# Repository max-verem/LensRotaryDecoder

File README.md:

# Lens Rotary Decoder

This project cover several cases on getting lens rotation info

## EZ-USB with Canon HJ14ex4.3B

This version cover getting virtual output of Canon HJ14ex4.3B lens output, please [follow](EZ-USB.md) detailed description

## MCU version

This version cover getting virtual output of Canon HJ14ex4.3B lens output and stanalone encoders, please [follow](MCU-NET.md) detailed description

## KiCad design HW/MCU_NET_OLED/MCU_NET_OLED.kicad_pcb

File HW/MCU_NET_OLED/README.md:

# MCU version of rotary decoder

This version cover both cases:
* Canon HJ14ex4.3B lens virtual output encoder
* Standalone rotary encoders

## Schematic

## PCB

[gerber file](gerber/)

## Firmware

* [rotary decoder firmware source](../../STM32/STM32F411CEU6_RotaryDecoder_3X)
* [NET OLED interface firmware source](../../STM32/STM32F411CEU6_FPGA_UART)

## Hardcoded things

* MAC address of this device is **BA:DE:C0:DE:XX:00** where **XX* is a *unique* hex value for that board
* IP address of FreeD receiver is broadcast (255.255.255.255), destination port is **60000** + **XX**

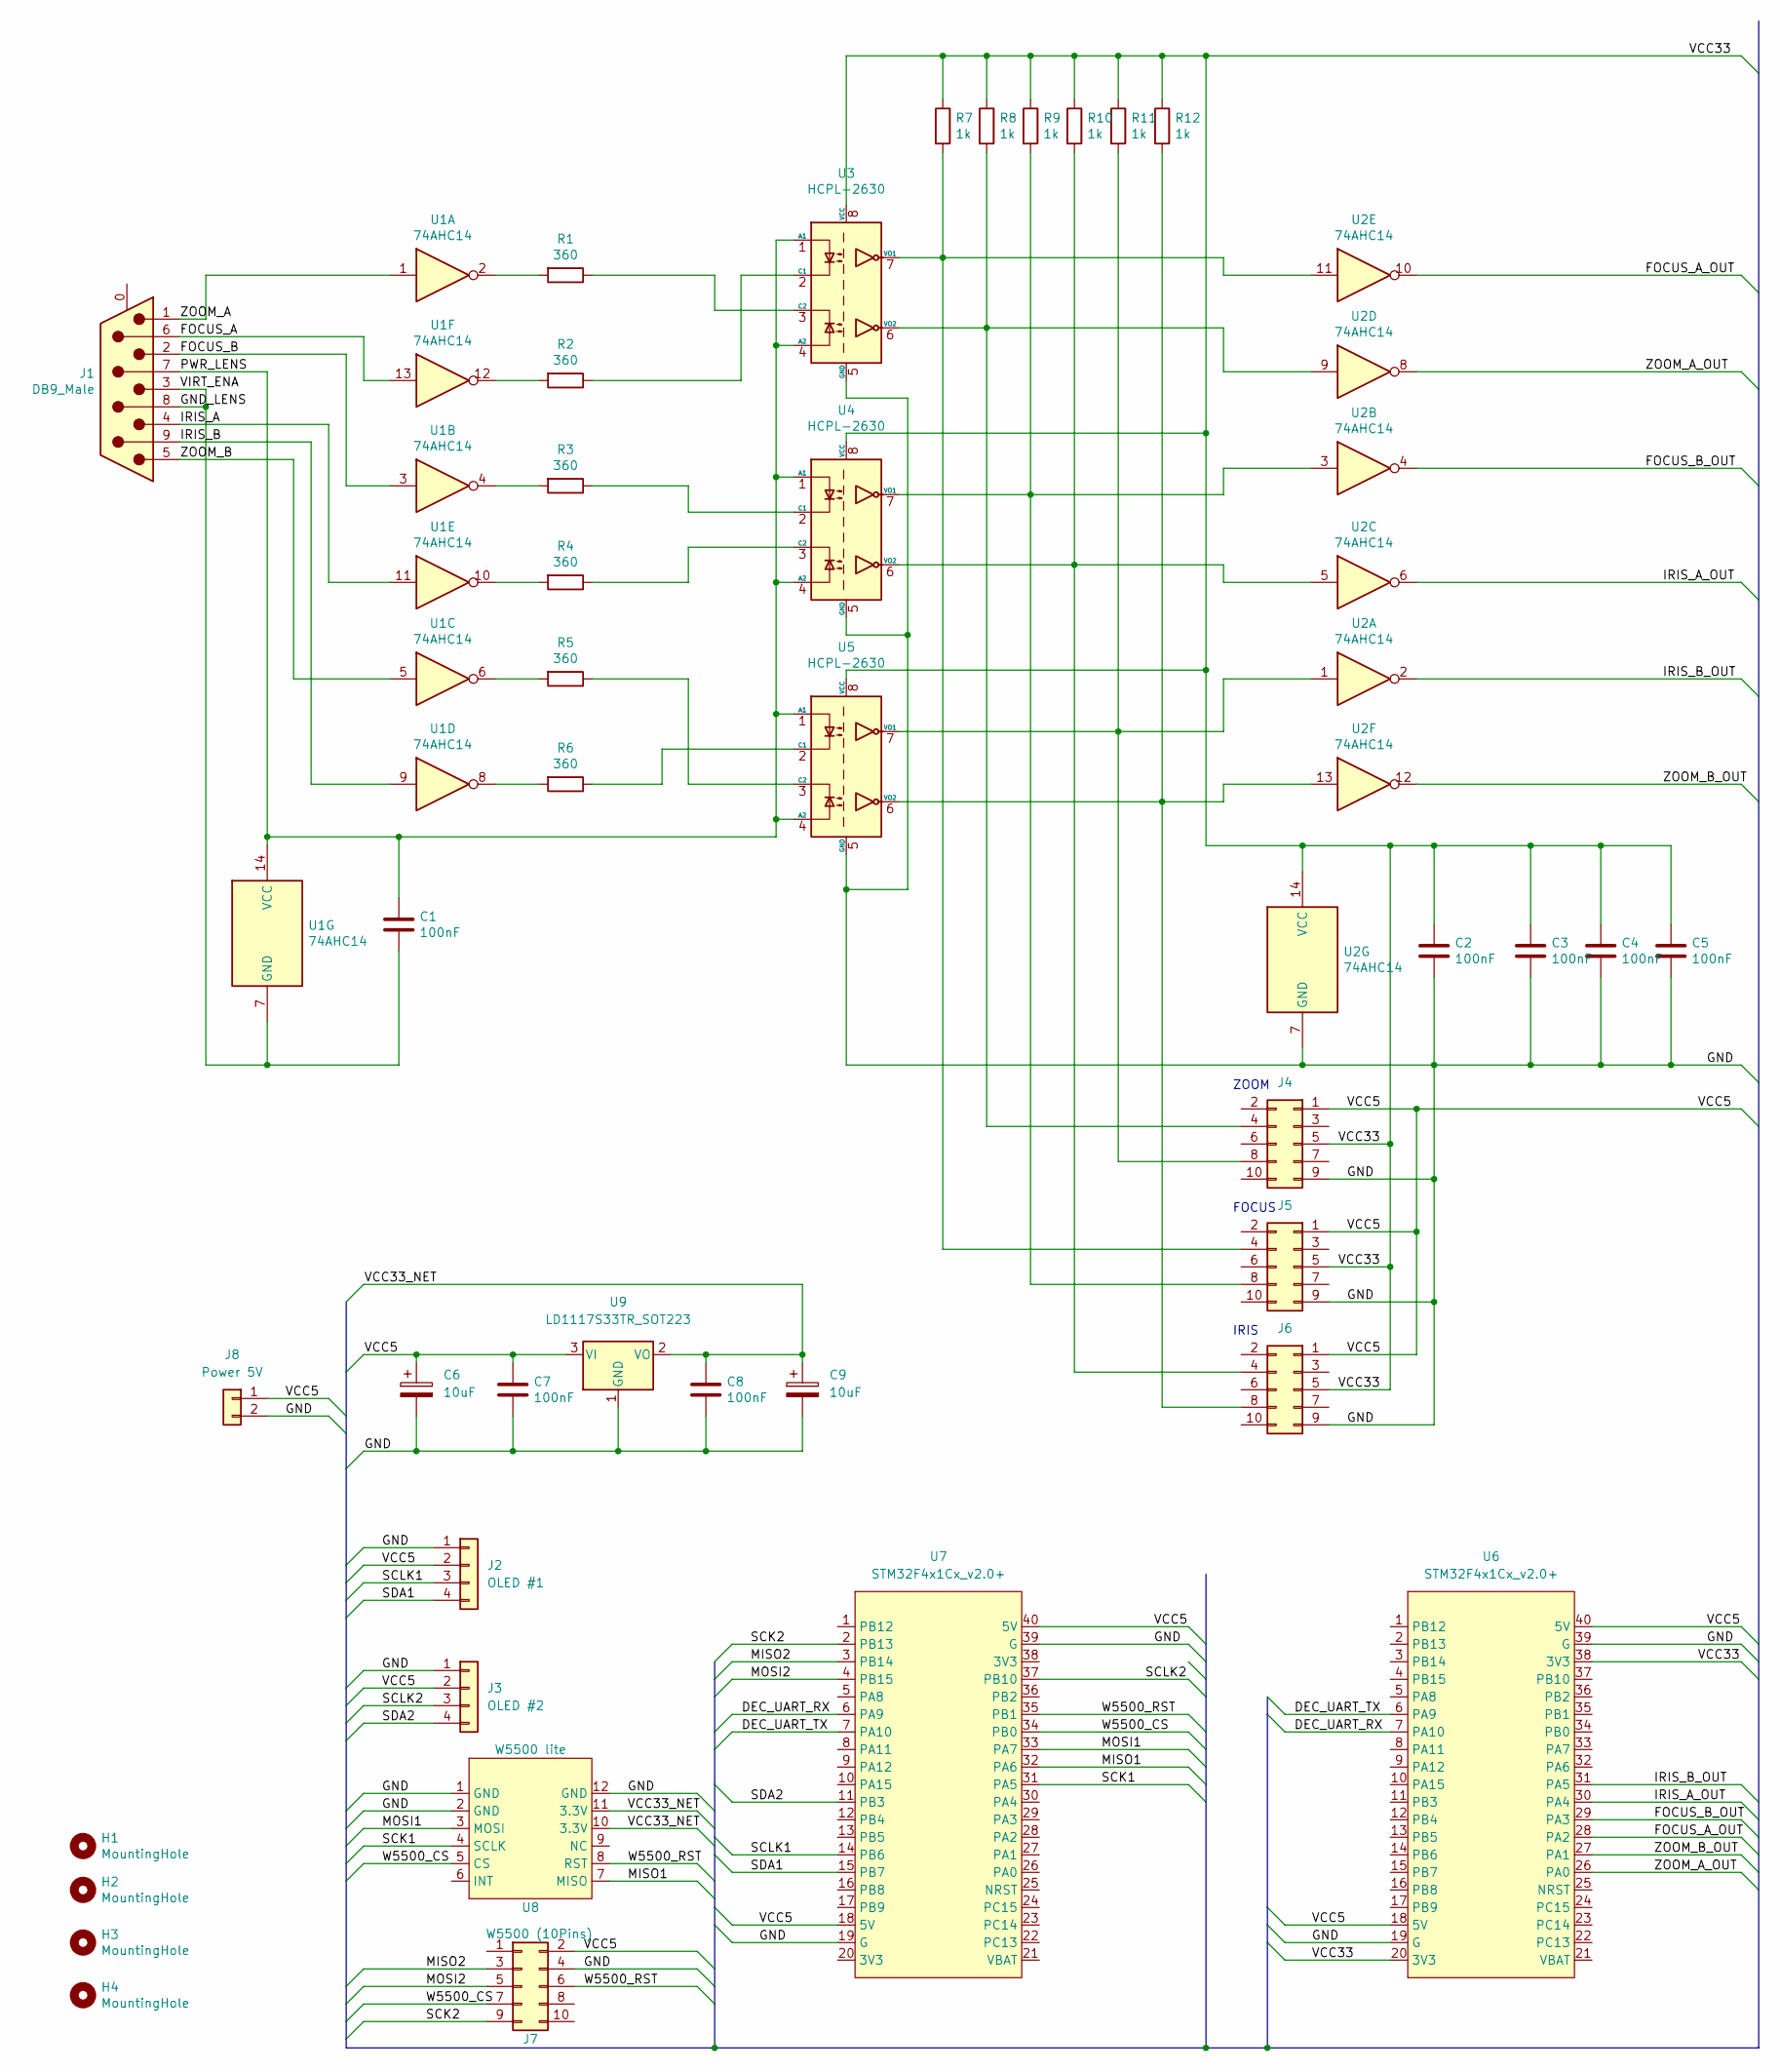
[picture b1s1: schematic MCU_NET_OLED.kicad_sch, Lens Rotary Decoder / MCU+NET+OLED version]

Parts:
C1, C2, C3, C4, C5, C7, C8: 100nF; C_Rect_L7.0mm_W2.0mm_P5.00mm
C6, C9: 10uF; C_Radial_D5.0mm_H11.0mm_P2.00mm
H1, H2, H3, H4: MountingHole; MountingHole_3.2mm_M3
J1: DB9_Male; DSUB-9_Male_Horizontal_P2.77x2.84mm_EdgePinOffset7.70mm_Hou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
J2: OLED #1; PinHeader_1x04_P2.54mm_Vertical
J3: OLED #2; PinHeader_1x04_P2.54mm_Vertical
J4, J5, J6: Conn_02x05_Odd_Even; IDC-Header_2x05_P2.54mm_Vertical
J7: W5500 (10Pins); IDC-Header_2x05_P2.54mm_Vertical
J8: Power 5V; JST_NV_B02P-NV_1x02_P5.00mm_Vertical
R1, R2, R3, R4, R5, R6: 360; R_Axial_DIN0309_L9.0mm_D3.2mm_P12.70mm_Horizontal
R7, R8, R9, R10, R11, R12: 1k; R_Axial_DIN0309_L9.0mm_D3.2mm_P12.70mm_Horizontal
U1, U2: 74AHC14; DIP-14_W7.62mm
U3, U4, U5: HCPL-2630; DIP-8_W7.62mm
U6, U7: STM32F4x1Cx_v2.0+; DIP-40_W15.24mm_LongPads
U8: W5500 lite; W5500
U9: LD1117S33TR_SOT223; SOT-223-3_TabPin2

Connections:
/DEC_UART_RX: U6.7 (PA10), U7.6 (PA9)
/DEC_UART_TX: U6.6 (PA9), U7.7 (PA10)
/FOCUS_A: J1.6, U1.13
/FOCUS_A_OUT: U2.10, U6.28 (PA2)
/FOCUS_B: J1.2, U1.3
/FOCUS_B_OUT: U2.4, U6.29 (PA3)
/GND: C2.2, C3.2, C4.2, C5.2, C6.2, C7.2, C8.2, C9.2, J2.1, J3.1, J4.9, J5.9, J6.9, J7.4, J8.2, U2.7 (GND), U3.5 (GND), U4.5 (GND), U5.5 (GND), U6.19 (G), U6.39 (G), U7.19 (G), U7.39 (G), U8.1 (GND), U8.2 (GND), U8.12 (GND), U9.1 (GND)
/GND_LENS: C1.2, J1.3, J1.8, U1.7 (GND)
/IRIS_A: J1.4, U1.11
/IRIS_A_OUT: U2.6, U6.30 (PA4)
/IRIS_B: J1.9, U1.9
/IRIS_B_OUT: U2.2, U6.31 (PA5)
/MISO1: U7.32 (PA6), U8.7 (MISO)
/MISO2: J7.3, U7.3 (PB14)
/MOSI1: U7.33 (PA7), U8.3 (MOSI)
/MOSI2: J7.5, U7.4 (PB15)
/PWR_LENS: C1.1, J1.7, U1.14 (VCC), U3.1 (A1), U3.4 (A2), U4.1 (A1), U4.4 (A2), U5.1 (A1), U5.4 (A2)
/SCK1: U7.31 (PA5), U8.4 (SCLK)
/SCK2: J7.9, U7.2 (PB13)
/SCLK1: J2.3, U7.14 (PB6)
/SCLK2: J3.3, U7.37 (PB10)
/SDA1: J2.4, U7.15 (PB7)
/SDA2: J3.4, U7.11 (PB3)
/VCC5: C6.1, C7.1, J2.2, J3.2, J4.1, J5.1, J6.1, J7.2, J8.1, U6.18 (5V), U6.40 (5V), U7.18 (5V), U7.40 (5V), U9.3 (VI)
/VCC33: C2.1, C3.1, C4.1, C5.1, J4.5, J5.5, J6.5, R7.1, R8.1, R9.1, R10.1, R11.1, R12.1, U2.14 (VCC), U3.8 (VCC), U4.8 (VCC), U5.8 (VCC), U6.20 (3V3), U6.38 (3V3)
/VCC33_NET: C8.1, C9.1, U8.10 (3.3V), U8.11 (3.3V), U9.2 (VO)
/W5500_CS: J7.7, U7.34 (PB0), U8.5 (CS)
/W5500_RST: J7.6, U7.35 (PB1), U8.8 (RST)
/ZOOM_A: J1.1, U1.1
/ZOOM_A_OUT: U2.8, U6.26 (PA0)
/ZOOM_B: J1.5, U1.5
/ZOOM_B_OUT: U2.12, U6.27 (PA1)
unnamed: R1.1, U3.3 (C2)
unnamed: R1.2, U1.2
unnamed: R2.1, U3.2 (C1)
unnamed: R2.2, U1.12
unnamed: R3.1, U4.2 (C1)
unnamed: R3.2, U1.4
unnamed: R4.1, U4.3 (C2)
unnamed: R4.2, U1.10
unnamed: R5.1, U5.3 (C2)
unnamed: R5.2, U1.6
unnamed: R6.2, U1.8
unnamed: J5.4, R7.2, U2.11, U3.7 (VO1)
unnamed: J4.4, R8.2, U2.9, U3.6 (VO2)
unnamed: J5.8, R9.2, U2.3, U4.7 (VO1)
unnamed: J6.4, R10.2, U2.5, U4.6 (VO2)
unnamed: J4.8, R11.2, U2.1, U5.7 (VO1)
unnamed: J6.8, R12.2, U2.13, U5.6 (VO2)
unnamed: R6.1, U5.2 (C1)

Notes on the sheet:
IRIS
FOCUS
ZOOM

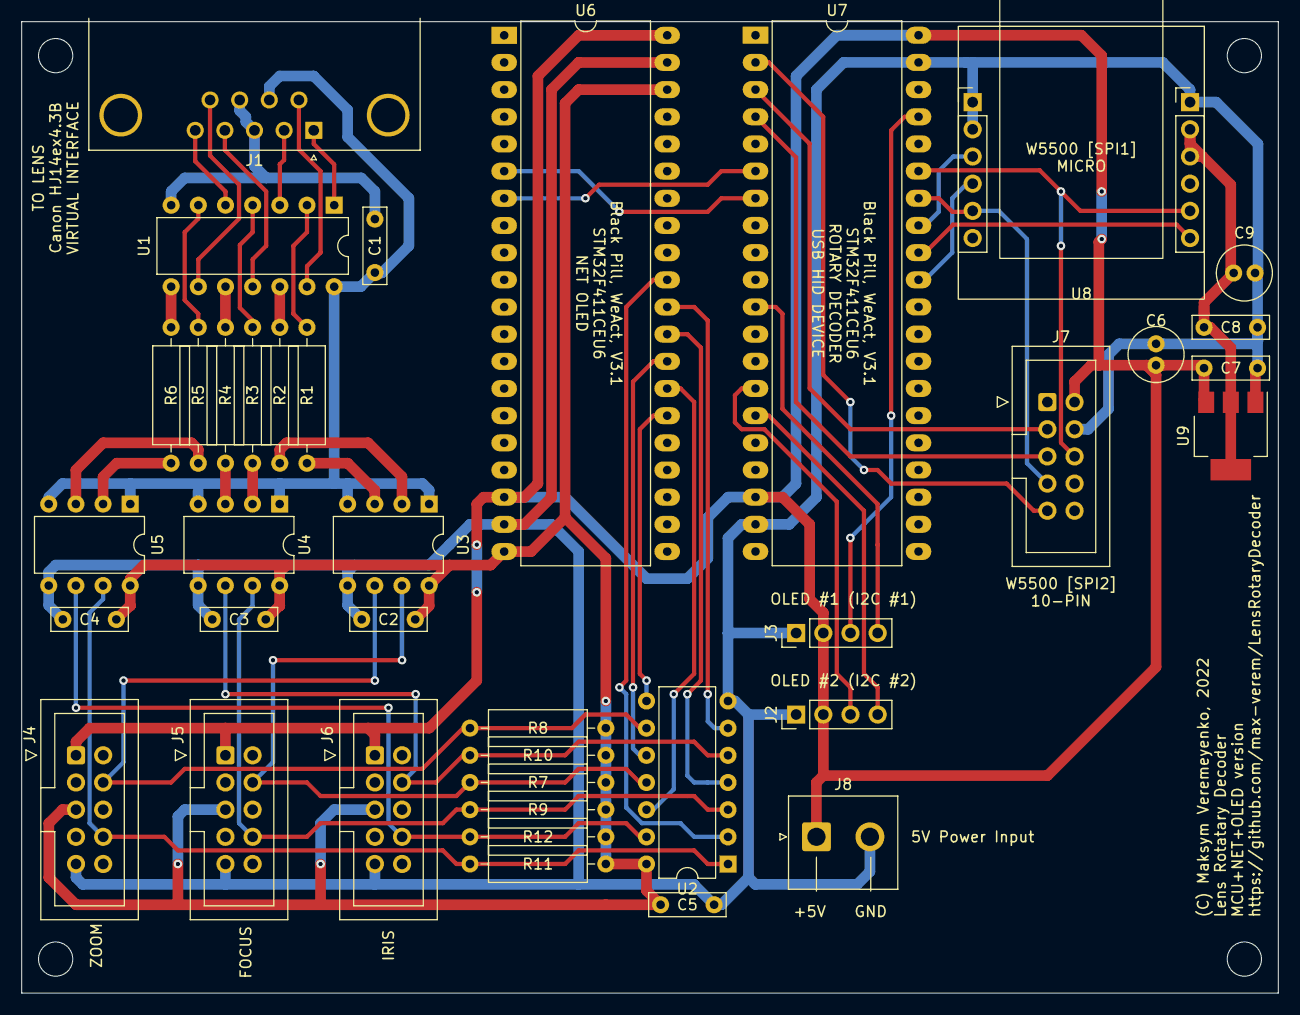
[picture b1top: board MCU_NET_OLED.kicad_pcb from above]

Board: 2 copper layers, 117.5 x 90.8 mm, 42 parts (0 on the bottom side), 50 nets.

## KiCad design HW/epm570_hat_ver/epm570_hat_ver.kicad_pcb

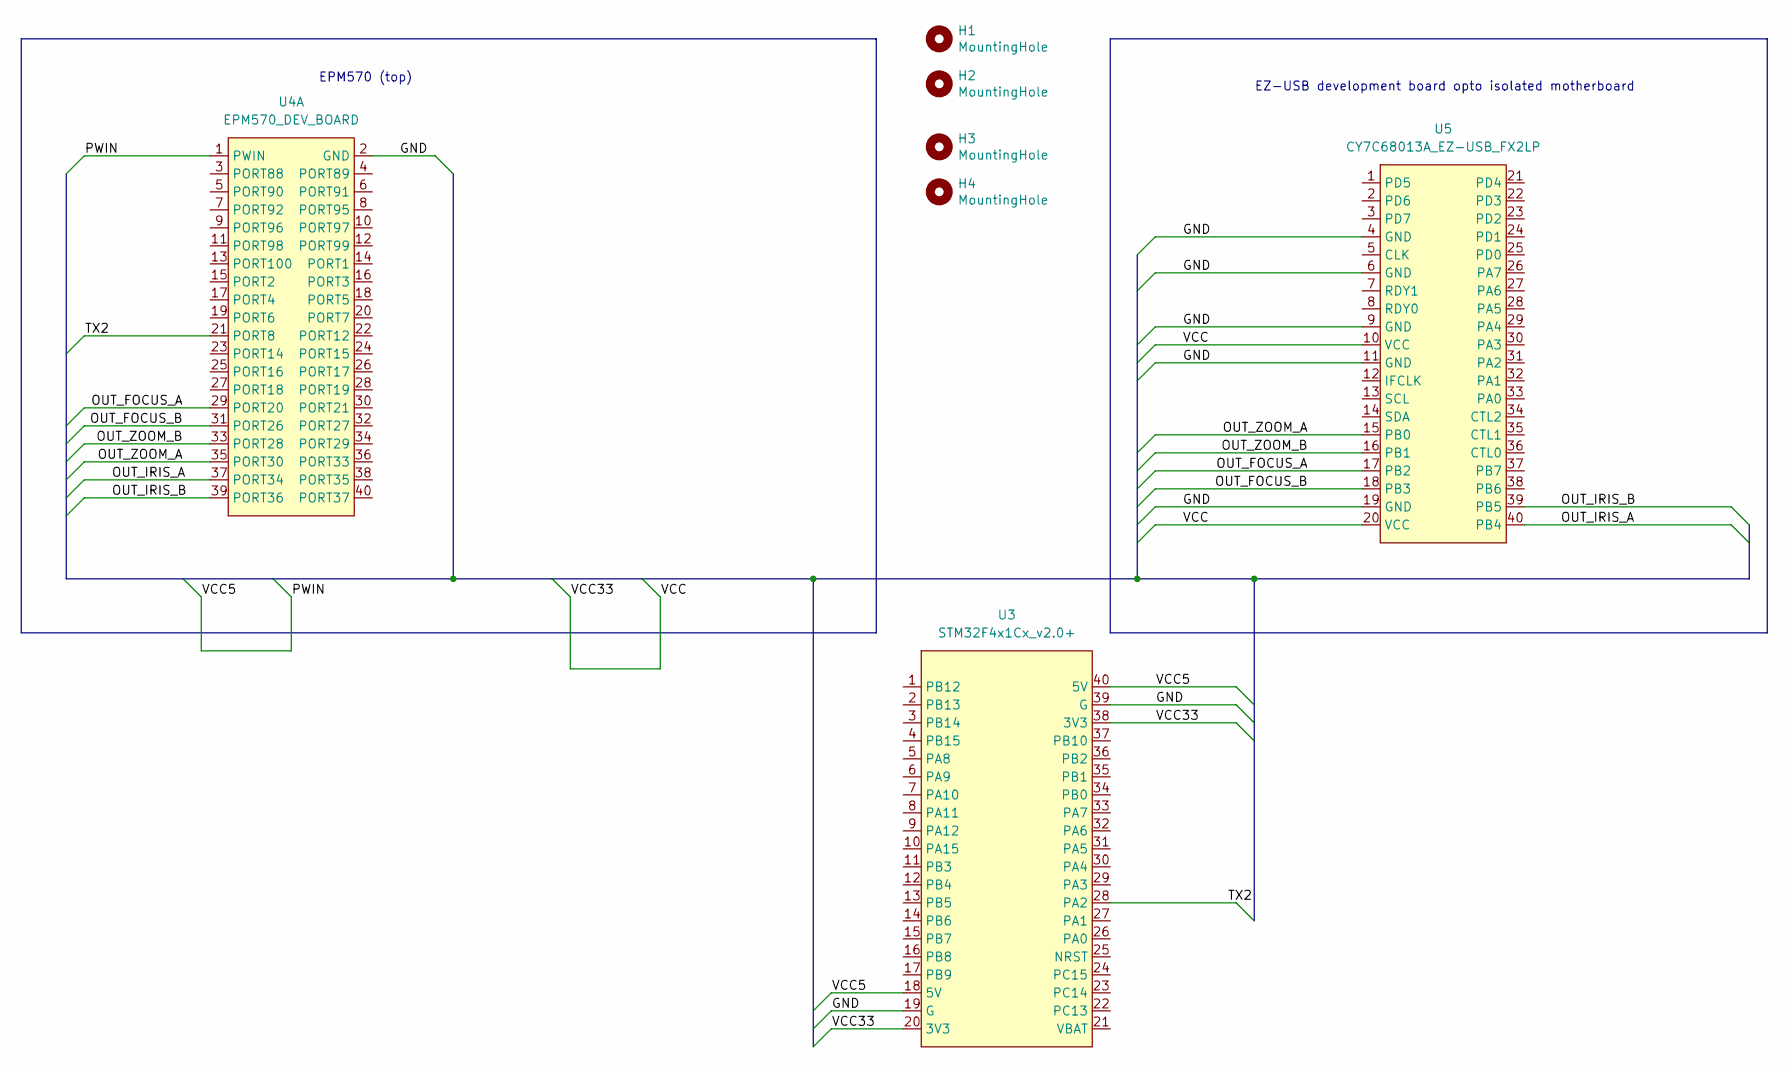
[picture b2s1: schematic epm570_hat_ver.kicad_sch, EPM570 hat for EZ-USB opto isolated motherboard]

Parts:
H1, H2, H3, H4: MountingHole; MountingHole_3.2mm_M3
U3: STM32F4x1Cx_v2.0+; DIP-40_W15.24mm_LongPads
U4: EPM570_DEV_BOARD; EPM570_DEV_BOARD_WEAK
U5: CY7C68013A_EZ-USB_FX2LP; CY7C68013A_EZ-USB_FX2LP_WEAK

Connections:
/GND: U3.19 (G), U3.39 (G), U4.2 (GND), U5.4 (GND), U5.6 (GND), U5.9 (GND), U5.11 (GND), U5.19 (GND)
/OUT_FOCUS_A: U4.29 (PORT20), U5.17 (PB2)
/OUT_FOCUS_B: U4.31 (PORT26), U5.18 (PB3)
/OUT_IRIS_A: U4.37 (PORT34), U5.40 (PB4)
/OUT_IRIS_B: U4.39 (PORT36), U5.39 (PB5)
/OUT_ZOOM_A: U4.35 (PORT30), U5.15 (PB0)
/OUT_ZOOM_B: U4.33 (PORT28), U5.16 (PB1)
/PWIN: U3.18 (5V), U3.40 (5V), U4.1 (PWIN)
/TX2: U3.28 (PA2), U4.21 (PORT8)
/VCC: U3.20 (3V3), U3.38 (3V3), U5.10 (VCC), U5.20 (VCC)

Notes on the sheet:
EZ-USB development board opto isolated motherboard
EPM570 (top)

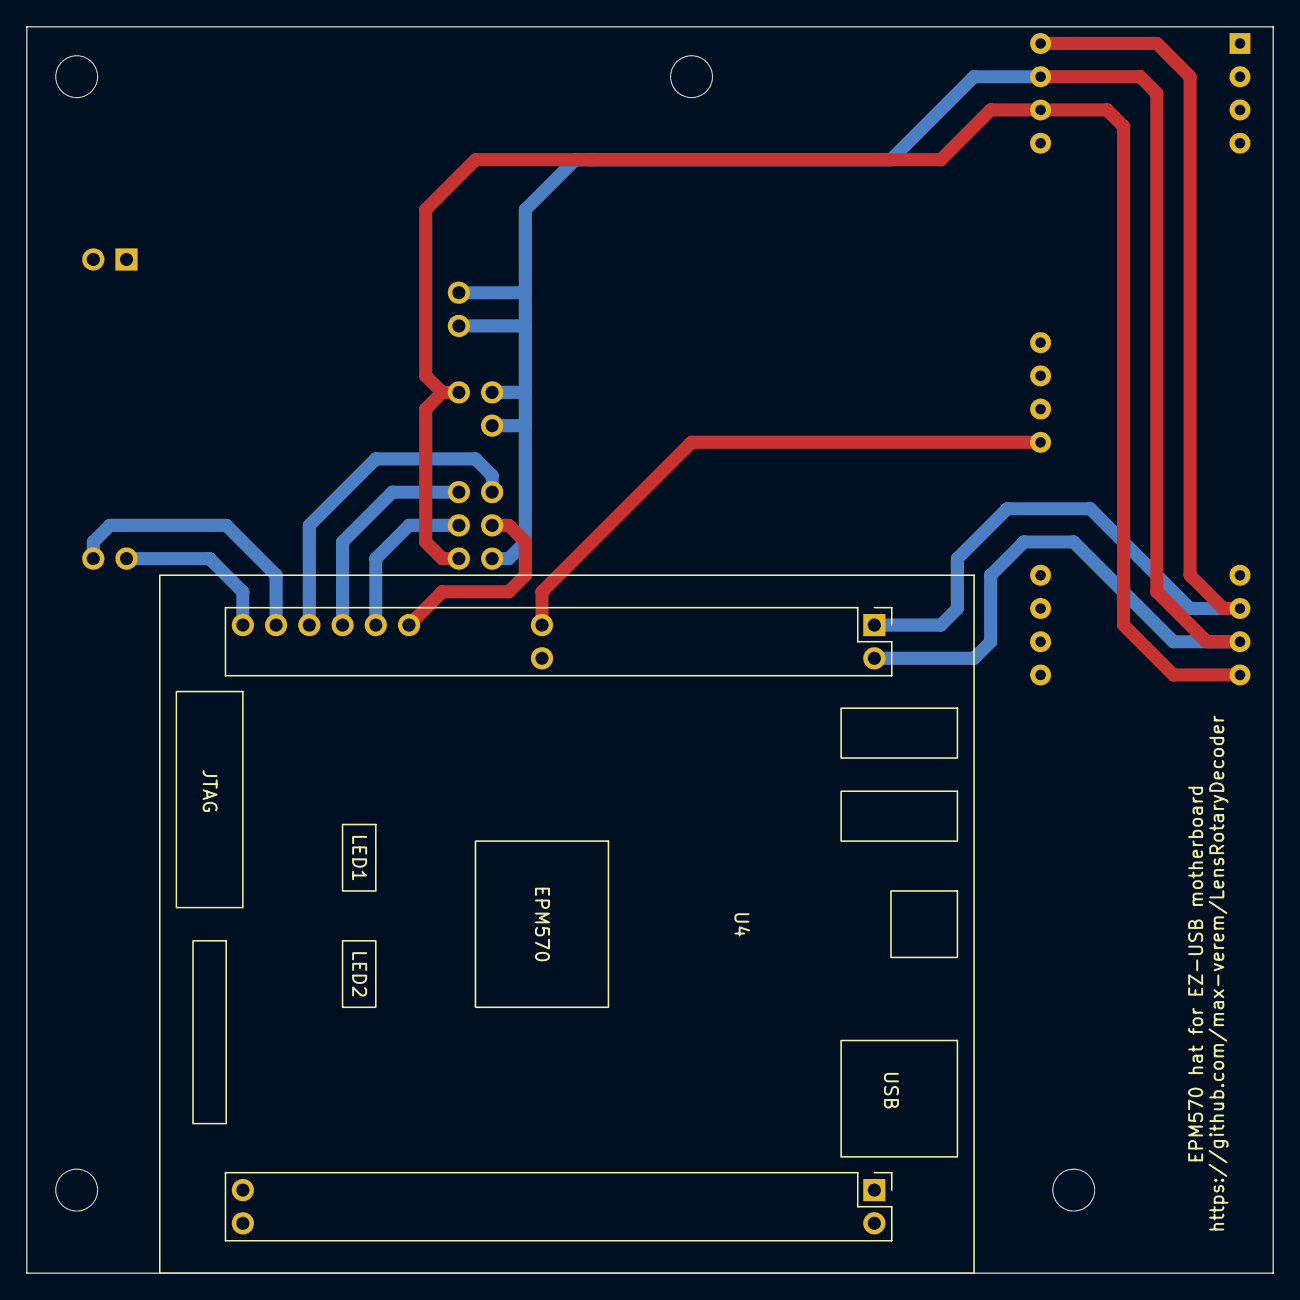
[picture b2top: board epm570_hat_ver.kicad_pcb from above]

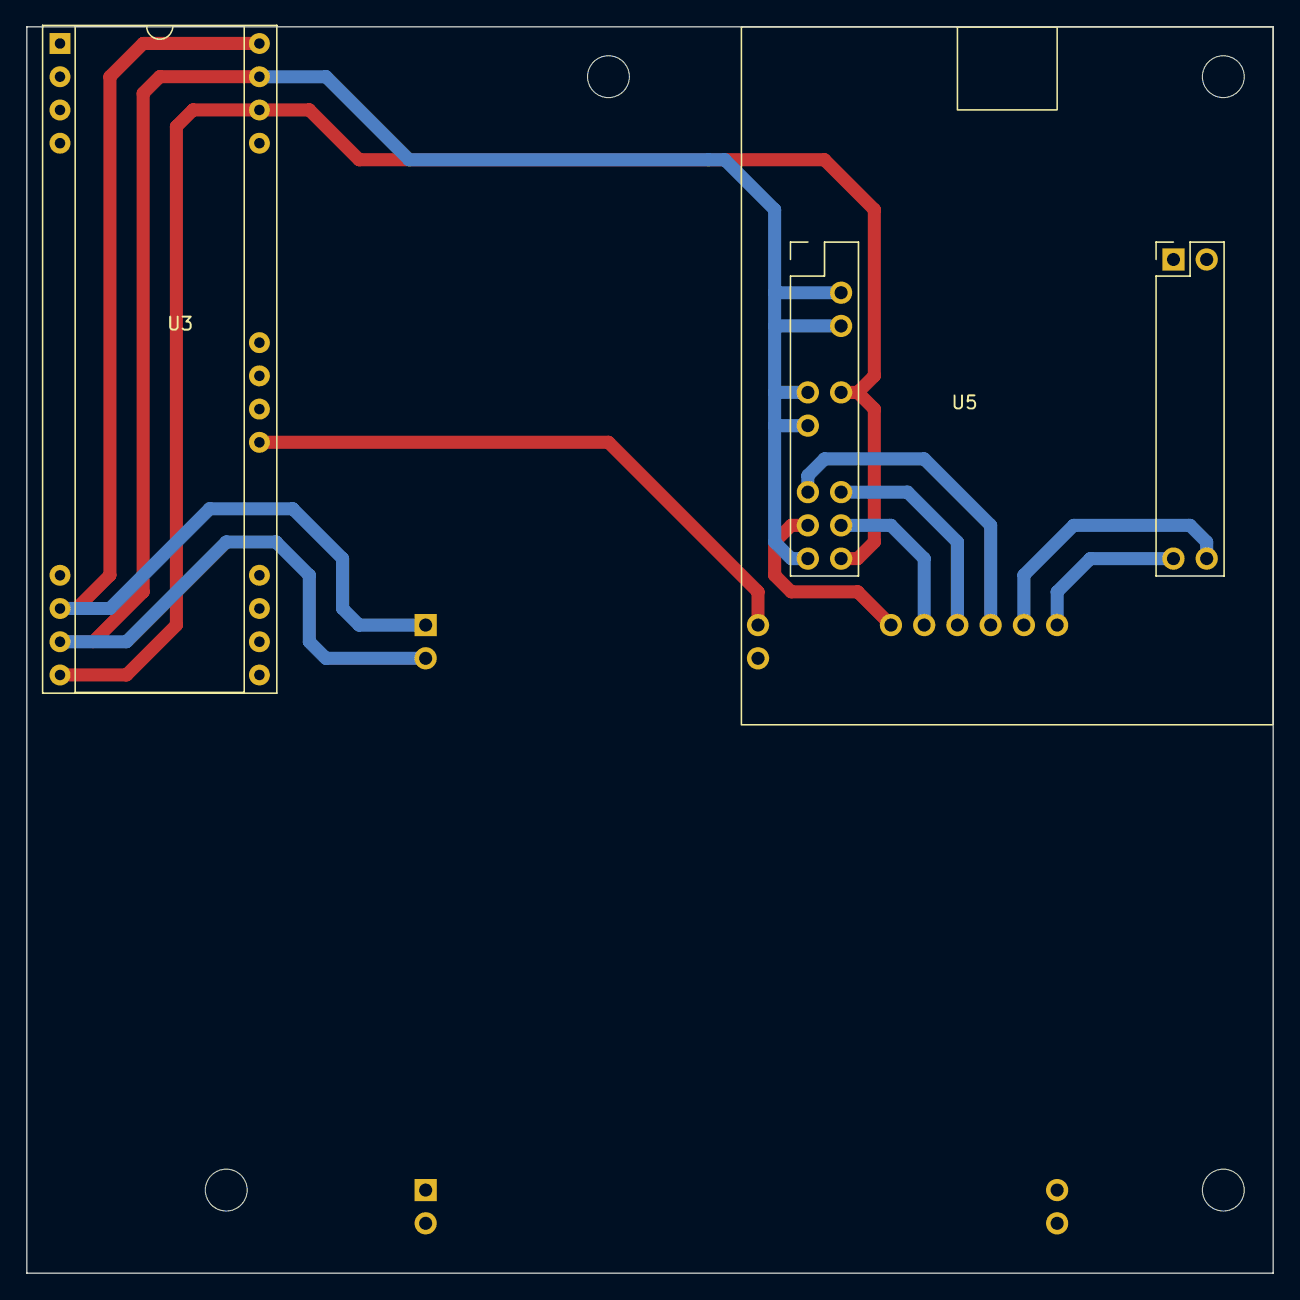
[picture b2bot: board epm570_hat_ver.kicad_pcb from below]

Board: 2 copper layers, 95.2 x 95.2 mm, 7 parts (2 on the bottom side), 10 nets.

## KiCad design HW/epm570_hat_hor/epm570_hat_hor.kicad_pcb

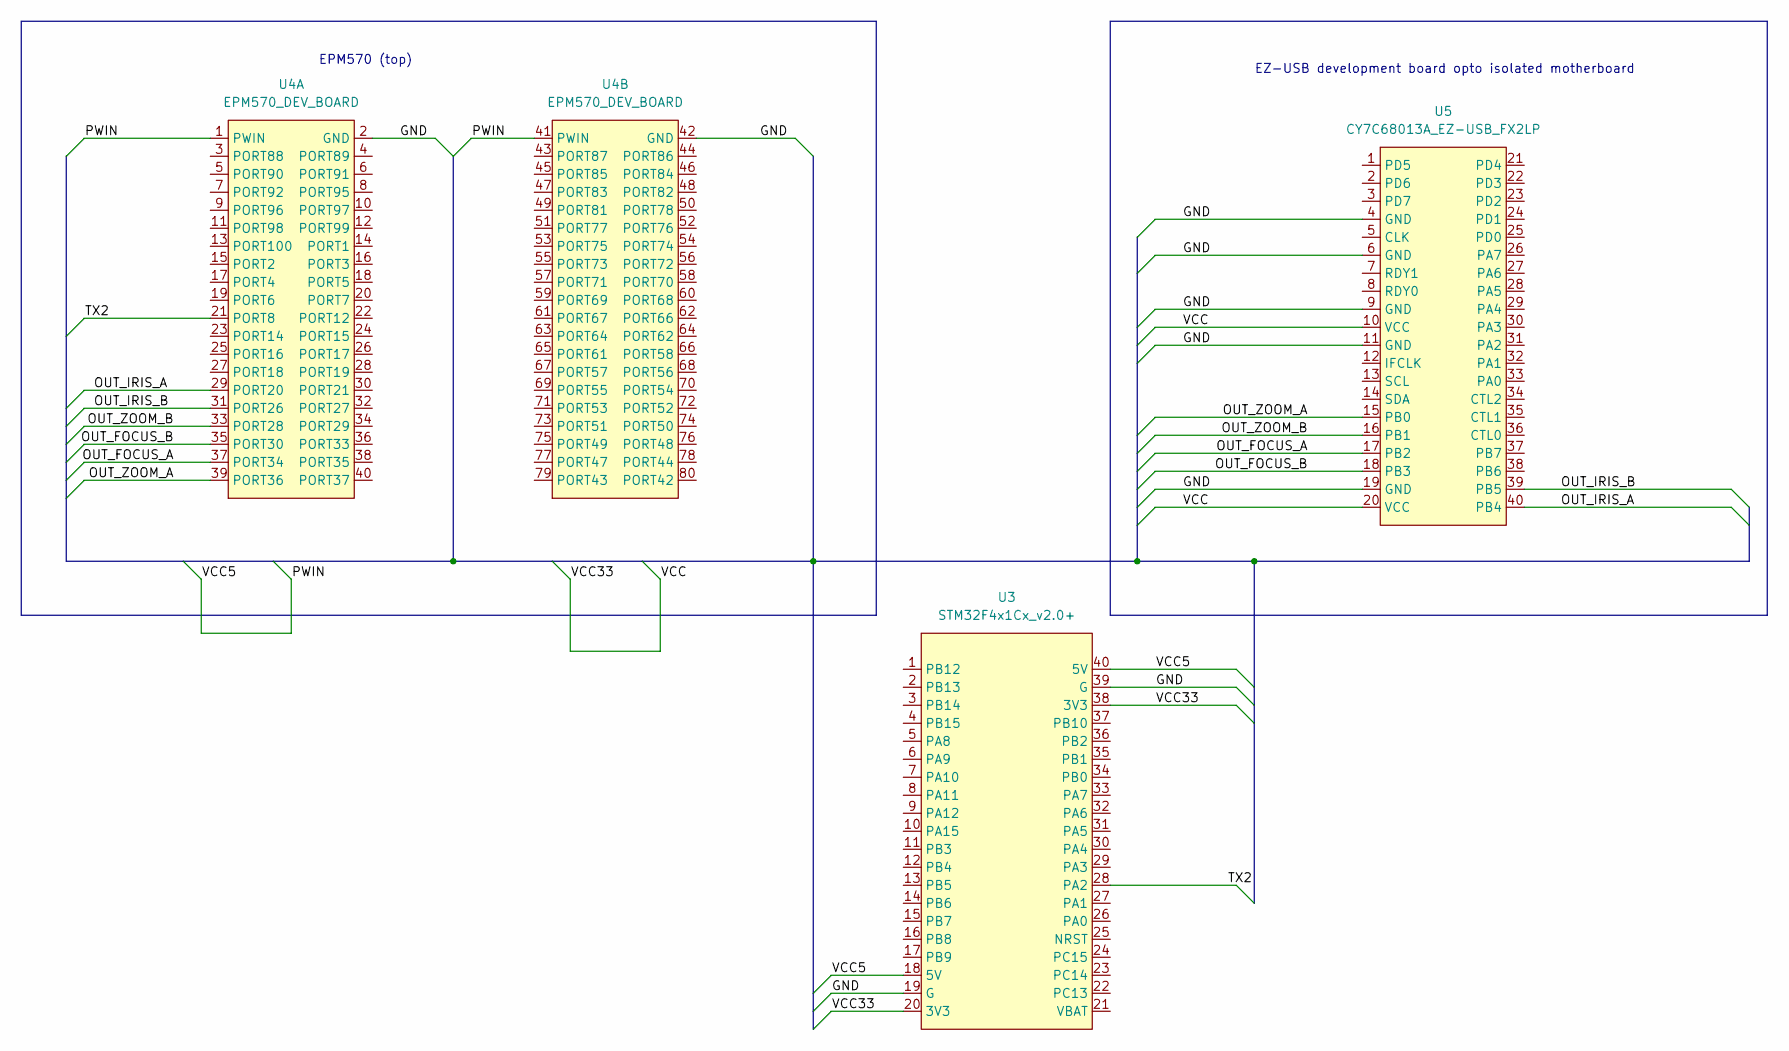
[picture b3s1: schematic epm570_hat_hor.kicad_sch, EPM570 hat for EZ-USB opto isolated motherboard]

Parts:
U3: STM32F4x1Cx_v2.0+; DIP-40_W15.24mm_LongPads
U4: EPM570_DEV_BOARD
U5: CY7C68013A_EZ-USB_FX2LP

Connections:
/GND: U3.19 (G), U3.39 (G), U4.2 (GND), U4.42 (GND), U5.4 (GND), U5.6 (GND), U5.9 (GND), U5.11 (GND), U5.19 (GND)
/OUT_FOCUS_A: U4.37 (PORT34), U5.17 (PB2)
/OUT_FOCUS_B: U4.35 (PORT30), U5.18 (PB3)
/OUT_IRIS_A: U4.29 (PORT20), U5.40 (PB4)
/OUT_IRIS_B: U4.31 (PORT26), U5.39 (PB5)
/OUT_ZOOM_A: U4.39 (PORT36), U5.15 (PB0)
/OUT_ZOOM_B: U4.33 (PORT28), U5.16 (PB1)
/PWIN: U3.18 (5V), U3.40 (5V), U4.1 (PWIN), U4.41 (PWIN)
/TX2: U3.28 (PA2), U4.21 (PORT8)
/VCC: U3.20 (3V3), U3.38 (3V3), U5.10 (VCC), U5.20 (VCC)

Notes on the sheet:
EZ-USB development board opto isolated motherboard
EPM570 (top)

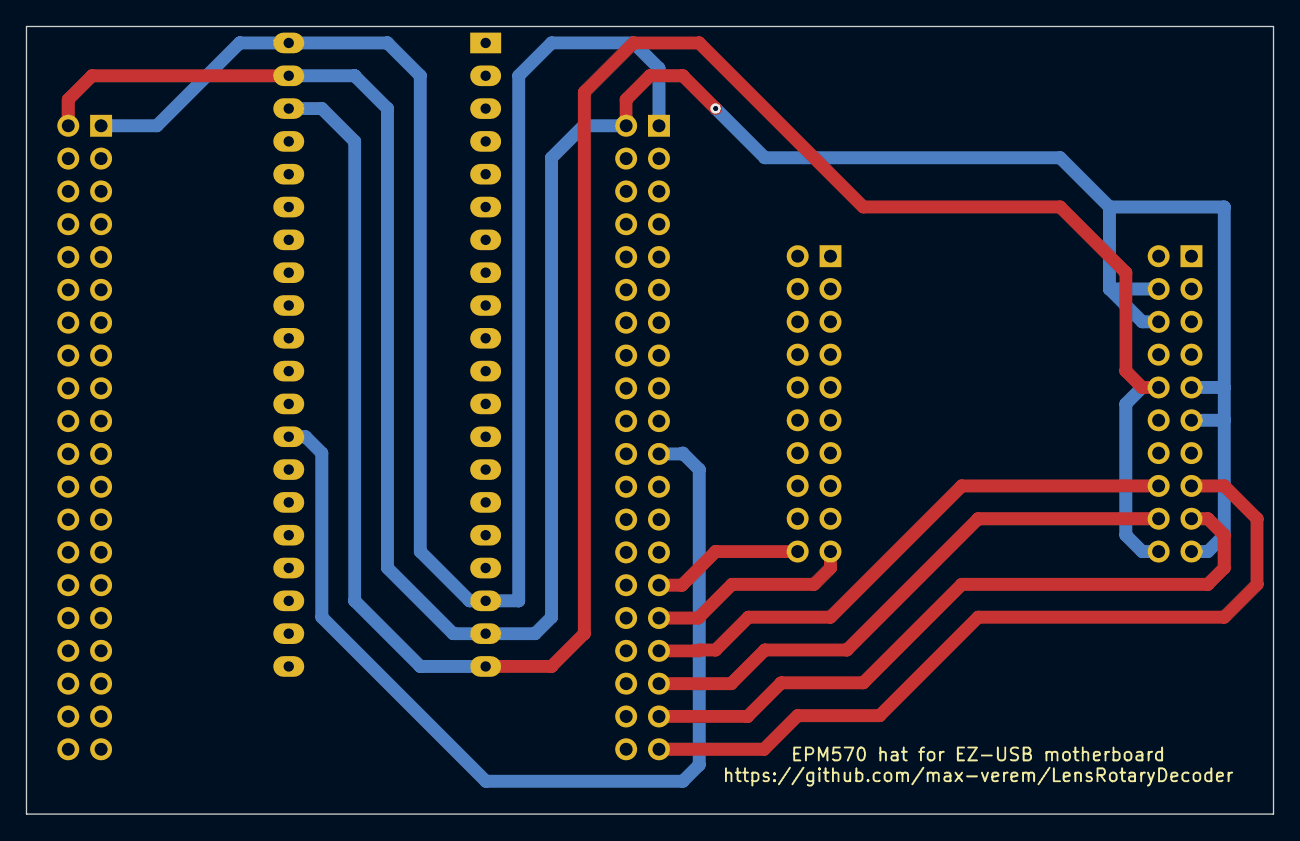
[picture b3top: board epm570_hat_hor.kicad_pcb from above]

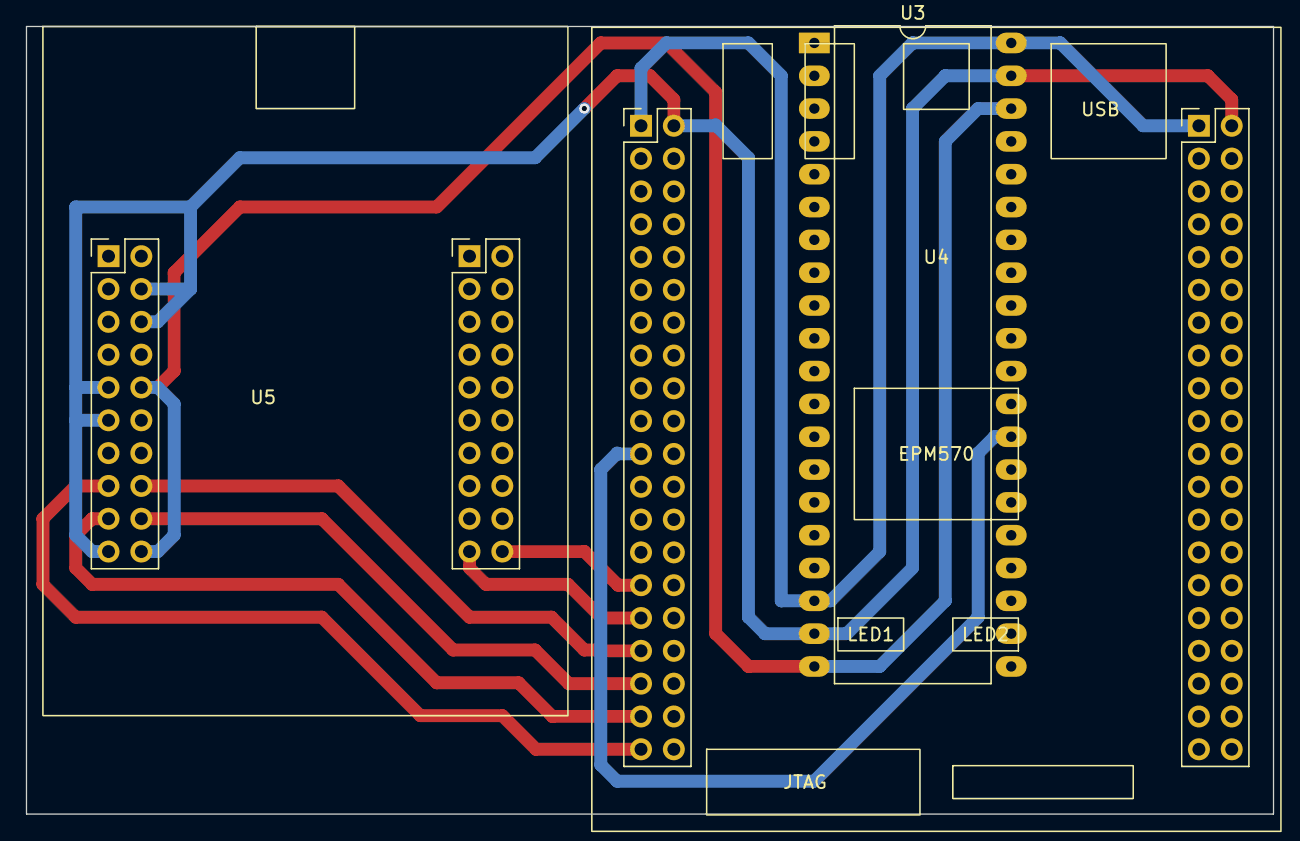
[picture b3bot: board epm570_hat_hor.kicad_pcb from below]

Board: 2 copper layers, 96.5 x 61.0 mm, 3 parts (3 on the bottom side), 10 nets.

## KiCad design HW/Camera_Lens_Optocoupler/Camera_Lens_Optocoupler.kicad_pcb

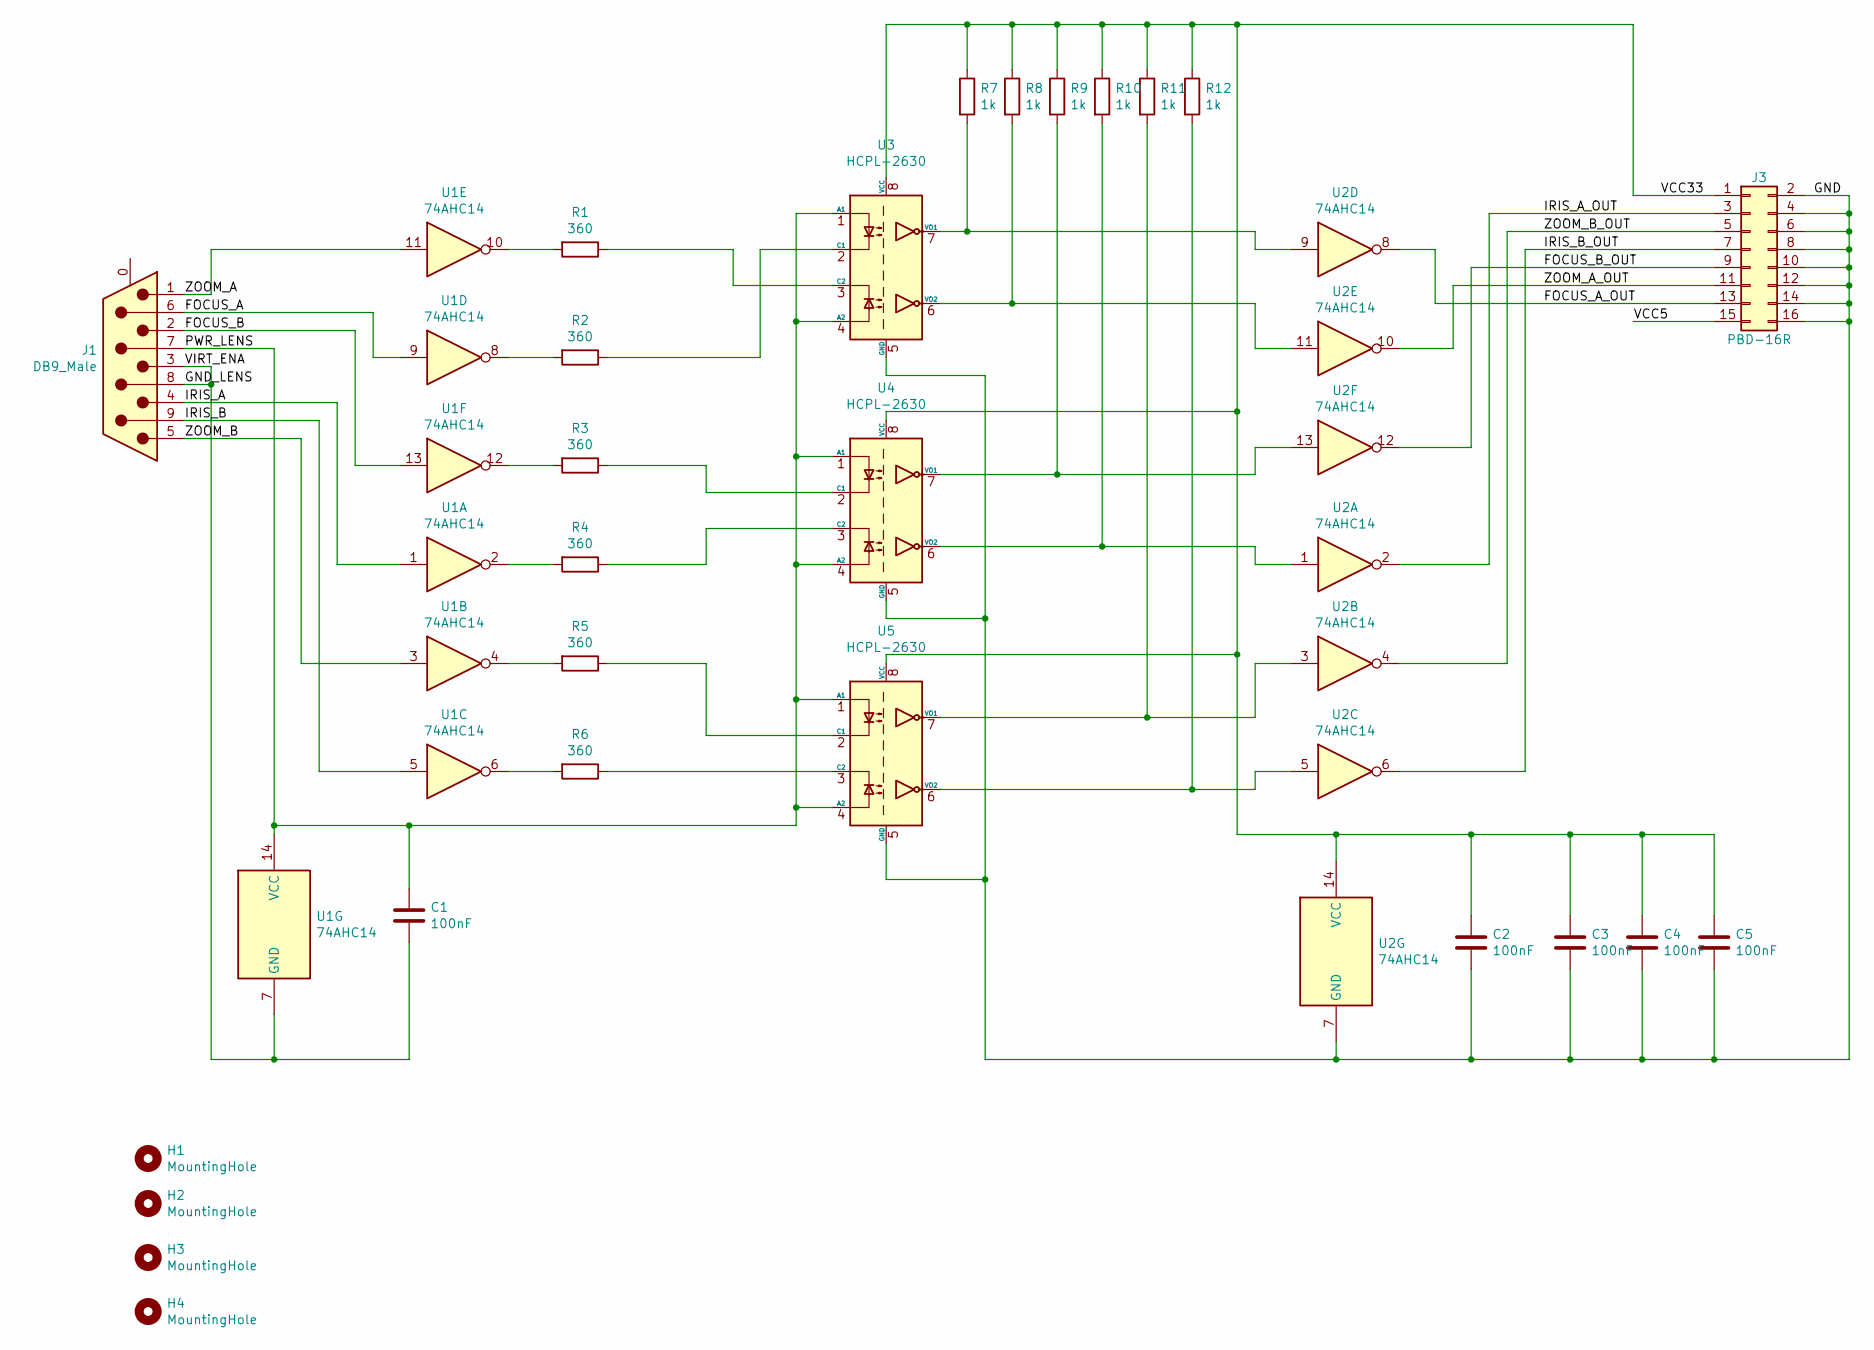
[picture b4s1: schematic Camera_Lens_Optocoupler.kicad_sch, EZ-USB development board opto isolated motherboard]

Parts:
C1, C2, C3, C4, C5: 100nF; C_Rect_L7.0mm_W2.0mm_P5.00mm
H1, H2, H3, H4: MountingHole; MountingHole_3.2mm_M3
J1: DB9_Male; DSUB-9_Male_Horizontal_P2.77x2.84mm_EdgePinOffset7.70mm_Hou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
J3: PBD-16R; PinSocket_2x08_P2.54mm_Horizontal
R1, R2, R3, R4, R5, R6: 360; R_Axial_DIN0309_L9.0mm_D3.2mm_P12.70mm_Horizontal
R7, R8, R9, R10, R11, R12: 1k; R_Axial_DIN0309_L9.0mm_D3.2mm_P12.70mm_Horizontal
U1, U2: 74AHC14; DIP-14_W7.62mm
U3, U4, U5: HCPL-2630; DIP-8_W7.62mm

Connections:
/FOCUS_A: J1.6, U1.9
/FOCUS_A_OUT: J3.13, U2.8
/FOCUS_B: J1.2, U1.13
/FOCUS_B_OUT: J3.9, U2.12
/GND: C2.2, C3.2, C4.2, C5.2, J3.2, J3.4, J3.6, J3.8, J3.10, J3.12, J3.14, J3.16, U2.7 (GND), U3.5 (GND), U4.5 (GND), U5.5 (GND)
/GND_LENS: C1.2, J1.3, J1.8, U1.7 (GND)
/IRIS_A: J1.4, U1.1
/IRIS_A_OUT: J3.3, U2.2
/IRIS_B: J1.9, U1.5
/IRIS_B_OUT: J3.7, U2.6
/PWR_LENS: C1.1, J1.7, U1.14 (VCC), U3.1 (A1), U3.4 (A2), U4.1 (A1), U4.4 (A2), U5.1 (A1), U5.4 (A2)
/VCC5: J3.15
/VCC33: C2.1, C3.1, C4.1, C5.1, J3.1, R7.1, R8.1, R9.1, R10.1, R11.1, R12.1, U2.14 (VCC), U3.8 (VCC), U4.8 (VCC), U5.8 (VCC)
/ZOOM_A: J1.1, U1.11
/ZOOM_A_OUT: J3.11, U2.10
/ZOOM_B: J1.5, U1.3
/ZOOM_B_OUT: J3.5, U2.4
unnamed: R1.1, U3.3 (C2)
unnamed: R1.2, U1.10
unnamed: R2.2, U1.8
unnamed: R3.2, U1.12
unnamed: R4.2, U1.2
unnamed: R5.2, U1.4
unnamed: R6.2, U1.6
unnamed: R7.2, U2.9, U3.7 (VO1)
unnamed: R8.2, U2.11, U3.6 (VO2)
unnamed: R9.2, U2.13, U4.7 (VO1)
unnamed: R10.2, U2.1, U4.6 (VO2)
unnamed: R11.2, U2.3, U5.7 (VO1)
unnamed: R12.2, U2.5, U5.6 (VO2)
unnamed: R2.1, U3.2 (C1)
unnamed: R3.1, U4.2 (C1)
unnamed: R4.1, U4.3 (C2)
unnamed: R5.1, U5.2 (C1)
unnamed: R6.1, U5.3 (C2)

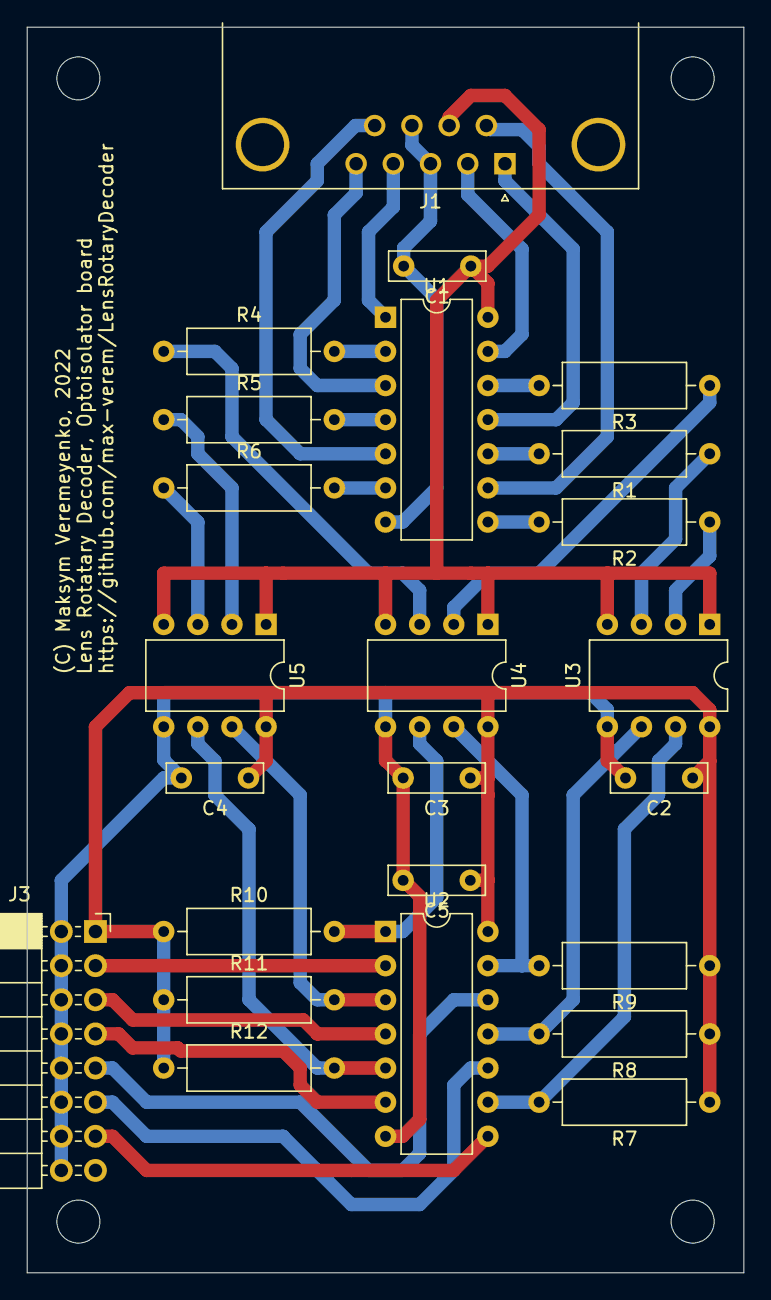
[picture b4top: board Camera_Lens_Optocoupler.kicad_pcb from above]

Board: 2 copper layers, 53.3 x 92.7 mm, 28 parts (0 on the bottom side), 34 nets.
